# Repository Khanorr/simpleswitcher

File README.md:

# simpleswitcher
A simple 2 group in 1 group out relay switcher

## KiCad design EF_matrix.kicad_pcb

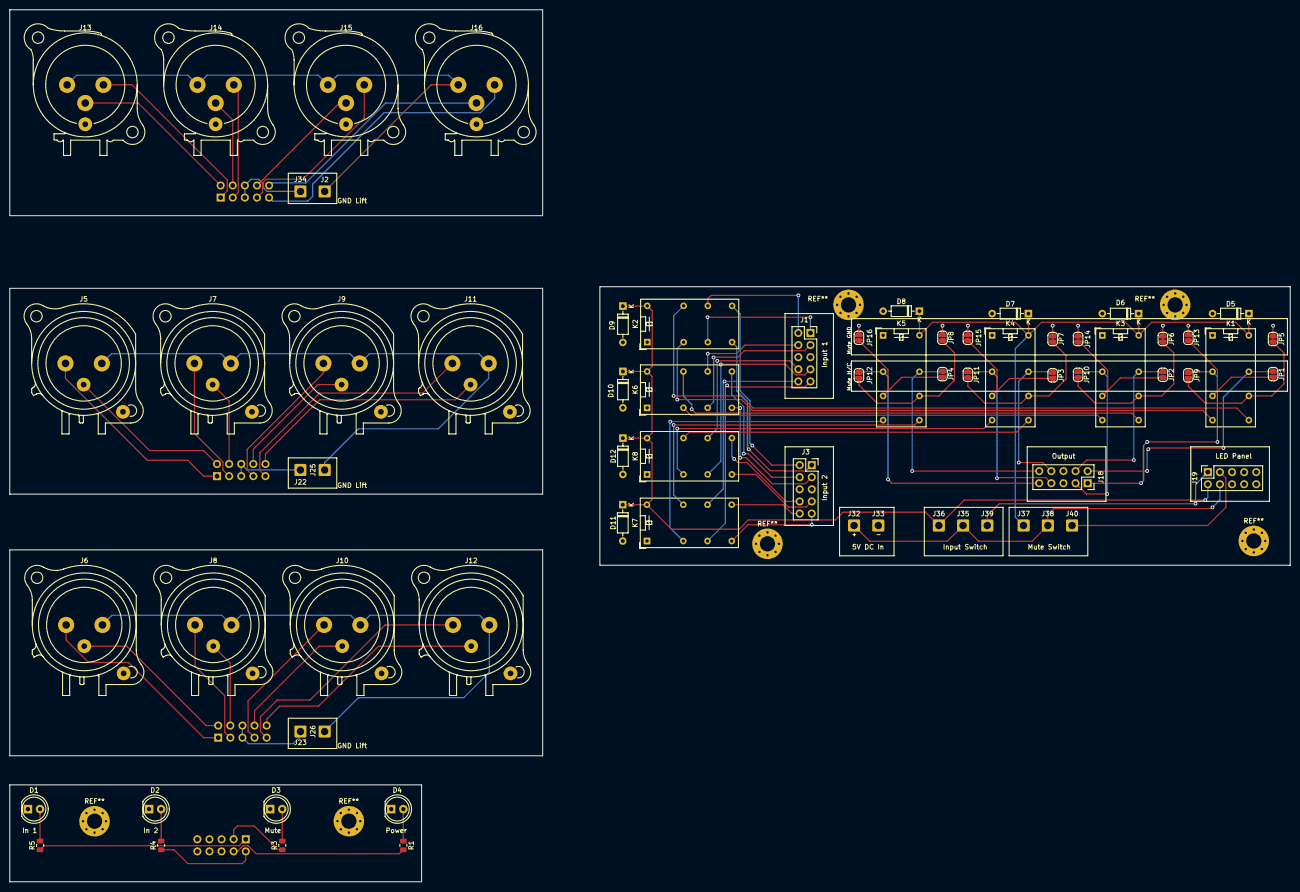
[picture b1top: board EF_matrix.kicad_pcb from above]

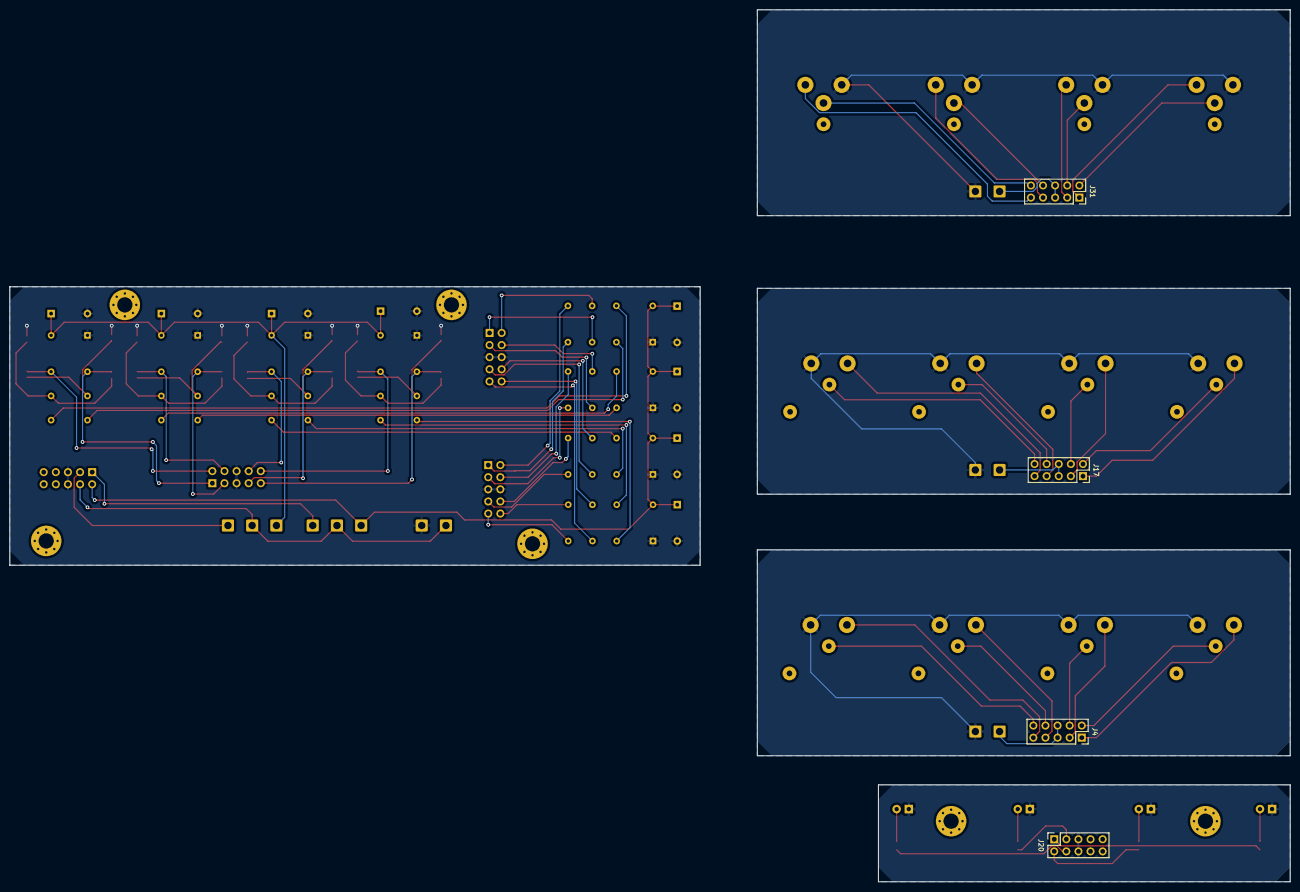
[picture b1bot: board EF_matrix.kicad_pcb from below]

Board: 2 copper layers, 268.6 x 182.9 mm, 74 parts (4 on the bottom side), 85 nets.

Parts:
D1, D2, D3, D4: LED; LED_D5.0mm
D5, D6, D7, D8, D9, D10, D11, D12: 1N4148; D_DO-35_SOD27_P7.62mm_Horizontal
J1, J3, J4, J17, J18, J19, J20, J31: Conn_02x05_Counter_Clockwise; PinSocket_2x05_P2.54mm_Vertical
J2, J22, J23, J25, J26, J32, J33, J34, J35, J36, J37, J38, J39, J40: Conn_01x01_Socket; SolderWire-0.75sqmm_1x01_D1.25mm_OD2.3mm
J5, J6, J7, J8, J9, J10, J11, J12: NC3FAAV2; Jack_XLR_Neutrik_NC3FAAV2_Vertical
J13, J14, J15, J16: NC3MAAH; Jack_XLR_Neutrik_NC3MAAV_Vertical
JP1, JP2, JP3, JP4, JP5, JP6, JP7, JP8, JP9, JP10, JP11, JP12, JP13, JP14, JP15, JP16: SolderJumper_2_Open; SolderJumper-2_P1.3mm_Open_RoundedPad1.0x1.5mm
K1, K2, K3, K4, K5, K6, K7, K8: G5V-2; Relay_DPDT_Omron_G5V-2
R1, R3, R4, R5: 160; R_0805_2012Metric

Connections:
+5V: J19.4, J32.1, J35.1, J38.1
/Buttonpanel/5V: J20.4, R1.2
/Buttonpanel/G1LED: J20.1, R5.1
/Buttonpanel/G2LED: J20.2, R4.1
/Buttonpanel/Ground: D1.1 (K), D2.1 (K), D3.1 (K), D4.1 (K), J20.5, J20.6
/Buttonpanel/MuteLED: J20.3, R3.1
/Mute F/Control: D5.1 (K), D6.1 (K), D7.1 (K), D8.1 (K), J37.1, K1.16, K3.16, K4.16, K5.16
/Mute F/In 1: K5.8, K7.4
/Mute F/In 2: K5.9, K7.13
/Mute F/Out 1: J18.9, JP12.1 (A), K5.4
/Mute F/Out 2: J18.10, JP4.1 (A), K5.13
/Mute L/In 1: K1.8, K2.4
/Mute L/In 2: K1.9, K2.13
/Mute L/Out 1: J18.1, JP9.1 (A), K1.4
/Mute L/Out 2: J18.2, JP1.1 (A), K1.13
/Mute R/In 1: K3.8, K6.4
/Mute R/In 2: K3.9, K6.13
/Mute R/Out 1: J18.3, JP10.1 (A), K3.4
/Mute R/Out 2: J18.4, JP2.1 (A), K3.13
/Mute S/In 1: K4.8, K8.4
/Mute S/In 2: K4.9, K8.13
/Mute S/Out 1: J18.7, JP11.1 (A), K4.4
/Mute S/Out 2: J18.8, JP3.1 (A), K4.13
/Switch F/Cold 1 In: J1.10, K7.11
/Switch F/Cold 2 In: J3.10, K7.9
/Switch F/Control: D9.1 (K), D10.1 (K), D11.1 (K), D12.1 (K), J19.2, J36.1, K2.16, K6.16, K7.16, K8.16
/Switch F/Hot 1 In: J1.9, K7.6
/Switch F/Hot 2 In: J3.9, K7.8
/Switch L/Cold 1 In: J1.2, K2.11
/Switch L/Cold 2 In: J3.2, K2.9
/Switch L/Hot 1 In: J1.1, K2.6
/Switch L/Hot 2 In: J3.1, K2.8
/Switch R/Cold 1 In: J1.4, K6.11
/Switch R/Cold 2 In: J3.4, K6.9
/Switch R/Hot 1 In: J1.3, K6.6
/Switch R/Hot 2 In: J3.3, K6.8
/Switch S/Cold 1 In: J1.8, K8.11
/Switch S/Cold 2 In: J3.8, K8.9
/Switch S/Hot 1 In: J1.7, K8.6
/Switch S/Hot 2 In: J3.7, K8.8
/XLR Input 1/Channel 1 Cold: J5.3, J17.2
/XLR Input 1/Channel 1 Hot: J5.2, J17.1
/XLR Input 1/Channel 2 Cold: J7.3, J17.4
/XLR Input 1/Channel 2 Hot: J7.2, J17.3
/XLR Input 1/Channel 3 Cold: J9.3, J17.8
/XLR Input 1/Channel 3 Hot: J9.2, J17.7
/XLR Input 1/Channel 4 Cold: J11.3, J17.10
/XLR Input 1/Channel 4 Hot: J11.2, J17.9
/XLR Input 1/GND_Lift: J17.5, J17.6, J22.1
/XLR Input 1/Pin1: J5.1, J7.1, J9.1, J11.1, J25.1
/XLR Input 2/Channel 1 Cold: J4.2, J6.3
/XLR Input 2/Channel 1 Hot: J4.1, J6.2
/XLR Input 2/Channel 2 Cold: J4.4, J8.3
/XLR Input 2/Channel 2 Hot: J4.3, J8.2
/XLR Input 2/Channel 3 Cold: J4.8, J10.3
/XLR Input 2/Channel 3 Hot: J4.7, J10.2
/XLR Input 2/Channel 4 Cold: J4.10, J12.3
/XLR Input 2/Channel 4 Hot: J4.9, J12.2
/XLR Input 2/GND_Lift: J4.5, J4.6, J23.1
/XLR Input 2/Pin1: J6.1, J8.1, J10.1, J12.1, J26.1
/XLR Output/Channel 1 Cold: J13.3, J31.2
/XLR Output/Channel 1 Hot: J13.2, J31.1
/XLR Output/Channel 2 Cold: J14.3, J31.4
/XLR Output/Channel 2 Hot: J14.2, J31.3
/XLR Output/Channel 3 Cold: J15.3, J31.8
/XLR Output/Channel 3 Hot: J15.2, J31.7
/XLR Output/Channel 4 Cold: J16.3, J31.10
/XLR Output/Channel 4 Hot: J16.2, J31.9
/XLR Output/GND_Lift: J31.5, J31.6, J34.1
/XLR Output/Pin1: J2.1, J13.1, J14.1, J15.1, J16.1
GND: D5.2 (A), D6.2 (A), D7.2 (A), D8.2 (A), D9.2 (A), D10.2 (A), D11.2 (A), D12.2 (A), J1.5, J1.6, J3.5, J3.6, J18.5, J18.6, J19.5, J19.6, J33.1, JP5.1 (A), JP6.1 (A), JP7.1 (A), JP8.1 (A), JP13.2 (B), JP14.2 (B), JP15.2 (B), JP16.2 (B), K1.1, K2.1, K3.1, K4.1, K5.1, K6.1, K7.1, K8.1
unnamed: D1.2 (A), R5.2
unnamed: D2.2 (A), R4.2
unnamed: D3.2 (A), R3.2
unnamed: D4.2 (A), R1.1
unnamed: J19.1, J39.1
unnamed: J19.3, J40.1
unnamed: JP1.2 (B), JP13.1 (A), K1.6
unnamed: JP5.2 (B), JP9.2 (B), K1.11
unnamed: JP6.2 (B), JP10.2 (B), K3.11
unnamed: JP7.2 (B), JP11.2 (B), K4.11
unnamed: JP8.2 (B), JP12.2 (B), K5.11
unnamed: JP2.2 (B), JP14.1 (A), K3.6
unnamed: JP3.2 (B), JP15.1 (A), K4.6
unnamed: JP4.2 (B), JP16.1 (A), K5.6

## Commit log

2023-11-21 Simple version of input selection, pure analog
2023-11-21 Minor optical fixes
2023-11-21 Finished up PCB layout
2023-11-23 splitting out single pcb files for production
